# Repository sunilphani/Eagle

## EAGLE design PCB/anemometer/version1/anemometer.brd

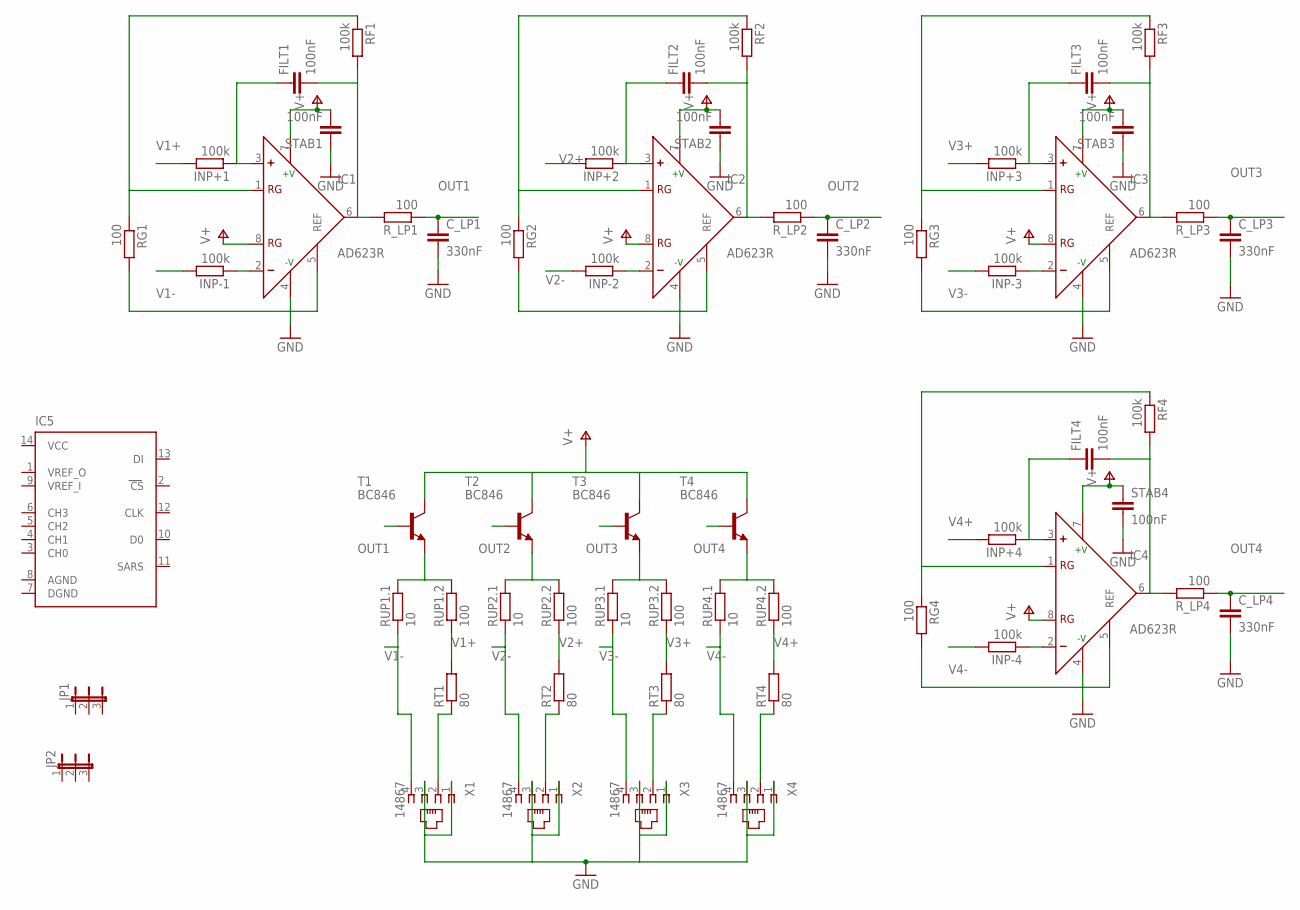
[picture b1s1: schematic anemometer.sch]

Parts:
C_LP1, C_LP2, C_LP3, C_LP4: 330nF; C1206
FILT1, FILT2, FILT3, FILT4: 100nF; C1206
IC1, IC2, IC3, IC4: AD623R; SO8
IC5: ADC08034D; SO14
INP+1, INP+2, INP+3, INP+4: 100k; M1206
INP-1, INP-2, INP-3, INP-4: 100k; M1206
JP1, JP2: JP2E; JP2
RF1, RF2, RF3, RF4: 100k; M1206
RG1, RG2, RG3, RG4: 100; M1206
RT1, RT2, RT3, RT4: 80; R1206
RUP1.1, RUP2.1, RUP3.1, RUP4.1: 10; R1206
RUP1.2, RUP2.2, RUP3.2, RUP4.2: 100; R1206
R_LP1, R_LP2, R_LP3, R_LP4: 100; M1206
STAB1, STAB2, STAB3, STAB4: 100nF; C1206
T1, T2, T3, T4: BC846; SOT23
X1, X2, X3, X4: 14867

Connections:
AGND: IC5.8 (AGND)
DGND: IC5.7 (DGND)
GND: C_LP1.2, C_LP2.2, C_LP3.2, C_LP4.2, IC1.4 (-V), IC1.5 (REF), IC2.4 (-V), IC2.5 (REF), IC3.4 (-V), IC3.5 (REF), IC4.4 (-V), IC4.5 (REF), RG1.2, RG2.2, RG3.2, RG4.2, STAB1.1, STAB2.1, STAB3.1, STAB4.2, X1.1, X1.3, X2.1, X2.3, X3.1, X3.3, X4.1, X4.3
unnamed: IC1.1 (RG), RF1.1, RG1.1
unnamed: IC4.1 (RG), RF4.1, RG4.1
unnamed: IC2.1 (RG), RF2.1, RG2.1
unnamed: IC3.1 (RG), RF3.1, RG3.1
unnamed: IC2.2 (-), INP-2.1
unnamed: IC1.2 (-), INP-1.1
unnamed: FILT2.1, IC2.3 (+), INP+2.1
unnamed: FILT3.1, IC3.3 (+), INP+3.1
unnamed: IC3.2 (-), INP-3.1
unnamed: FILT4.1, IC4.3 (+), INP+4.1
unnamed: IC4.2 (-), INP-4.1
unnamed: FILT1.1, IC1.3 (+), INP+1.1
OUT1: C_LP1.1, R_LP1.1, T1.1 (B)
OUT1.1: FILT1.2, IC1.6 (OUT), RF1.2, R_LP1.2
OUT2: C_LP2.1, R_LP2.1, T2.1 (B)
OUT2.1: FILT2.2, IC2.6 (OUT), RF2.2, R_LP2.2
OUT3: C_LP3.1, R_LP3.1, T3.1 (B)
OUT3.1: FILT3.2, IC3.6 (OUT), RF3.2, R_LP3.2
OUT4: C_LP4.1, R_LP4.1, T4.1 (B)
OUT4.1: FILT4.2, IC4.6 (OUT), RF4.2, R_LP4.2
REF1: RT1.1, X1.2
REF2: RT2.1, X2.2
REF3: RT3.1, X3.2
REF4: RT4.1, X4.2
SUPL1: RUP1.1.2, RUP1.2.2, T1.2 (E)
SUPL2: RUP2.1.2, RUP2.2.2, T2.2 (E)
SUPL3: RUP3.1.2, RUP3.2.2, T3.2 (E)
SUPL4: RUP4.1.2, RUP4.2.2, T4.2 (E)
V1+: INP+1.2, RT1.2, RUP1.2.1
V1-: INP-1.2, RUP1.1.1, X1.4
V2+: INP+2.2, RT2.2, RUP2.2.1
V2-: INP-2.2, RUP2.1.1, X2.4
V3+: INP+3.2, RT3.2, RUP3.2.1
V3-: INP-3.2, RUP3.1.1, X3.4
V4+: INP+4.2, RT4.2, RUP4.2.1
V4-: INP-4.2, RUP4.1.1, X4.4
V+: IC1.7 (+V), IC1.8 (RG), IC2.7 (+V), IC2.8 (RG), IC3.7 (+V), IC3.8 (RG), IC4.7 (+V), IC4.8 (RG), STAB1.2, STAB2.2, STAB3.2, STAB4.1, T1.3 (C), T2.3 (C), T3.3 (C), T4.3 (C)
VCC: IC5.14 (VCC)

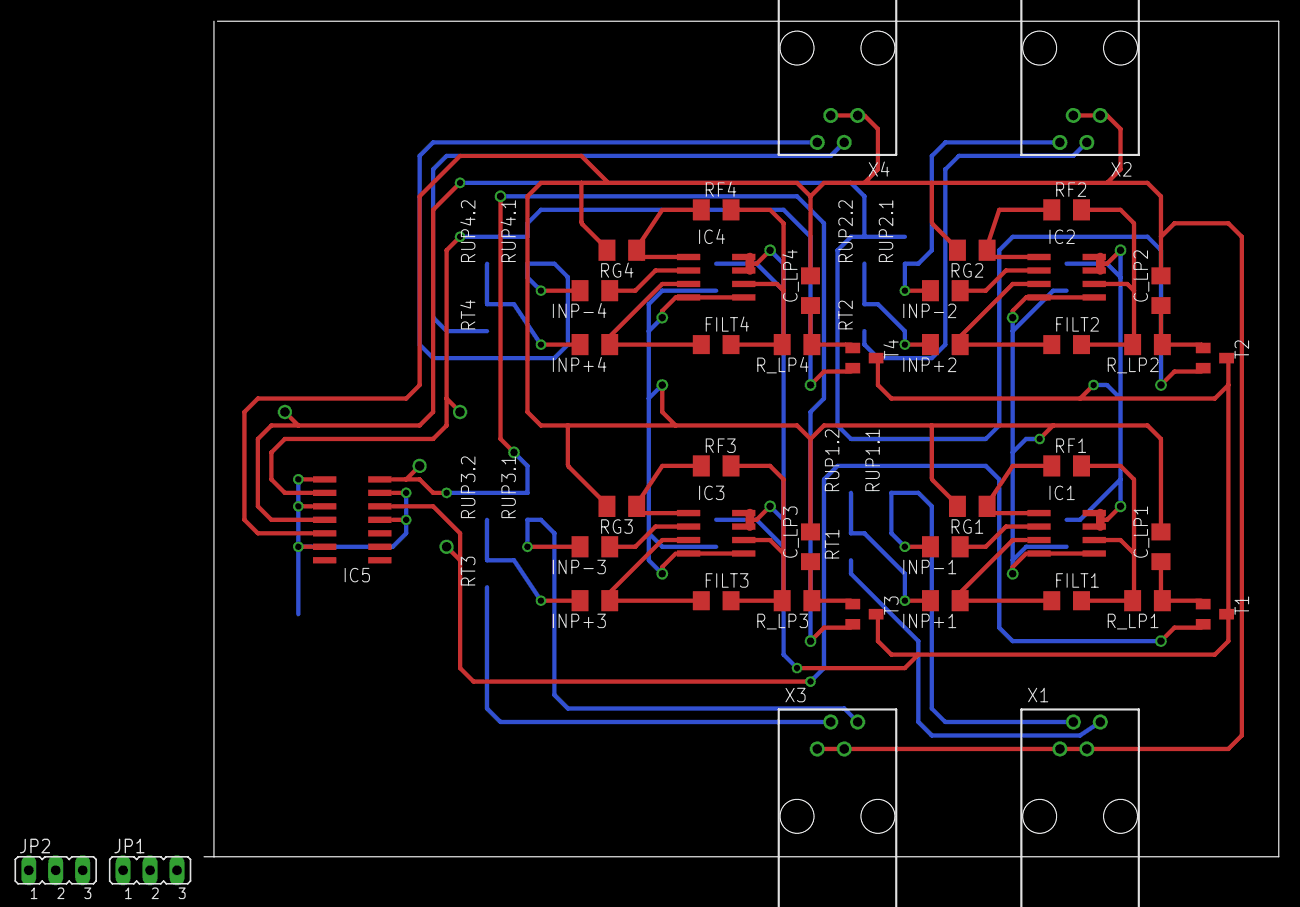
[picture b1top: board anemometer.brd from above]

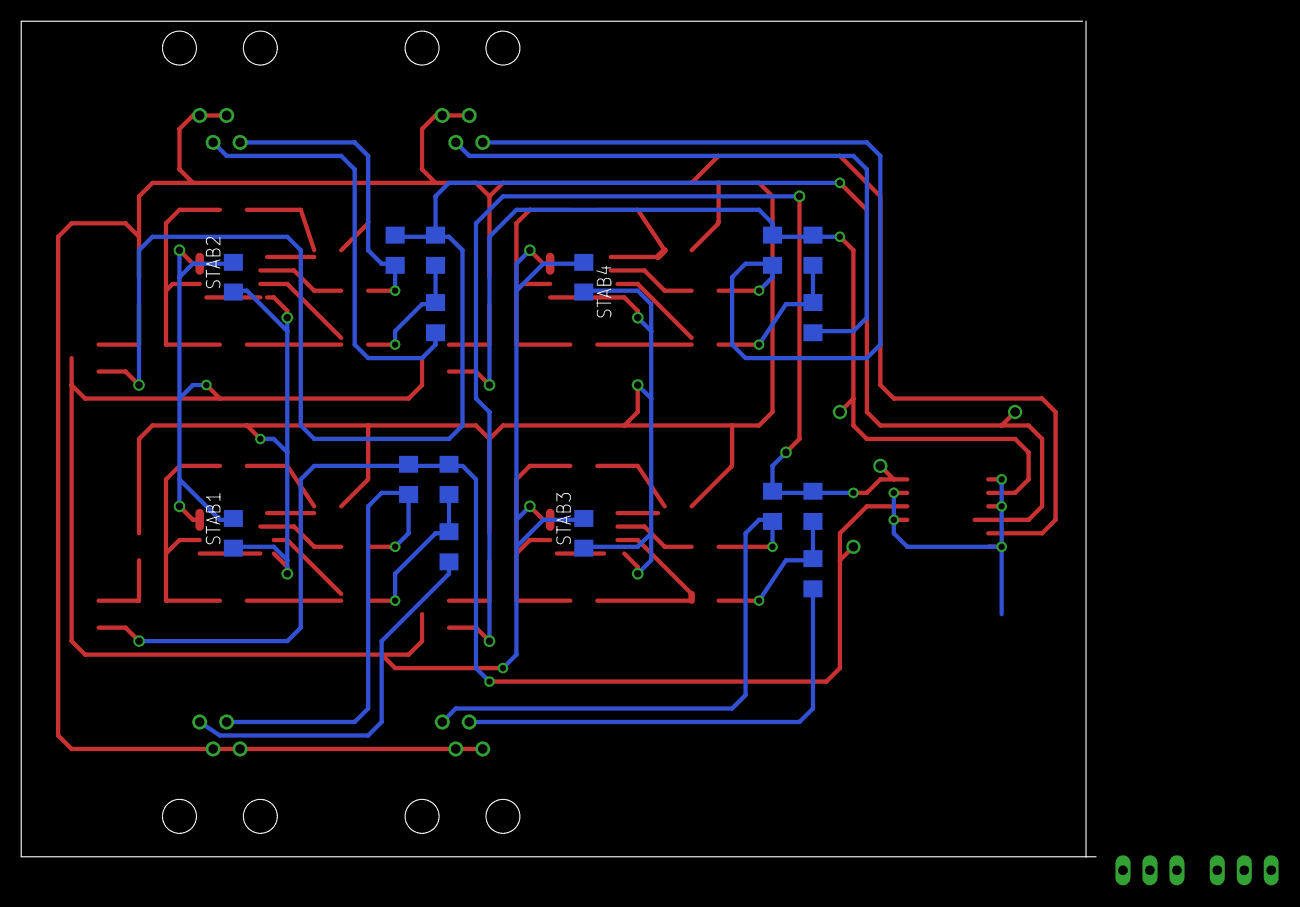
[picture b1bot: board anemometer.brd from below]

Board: 2 copper layers, 101.3 x 78.7 mm, 59 parts (4 on the bottom side), 38 nets.

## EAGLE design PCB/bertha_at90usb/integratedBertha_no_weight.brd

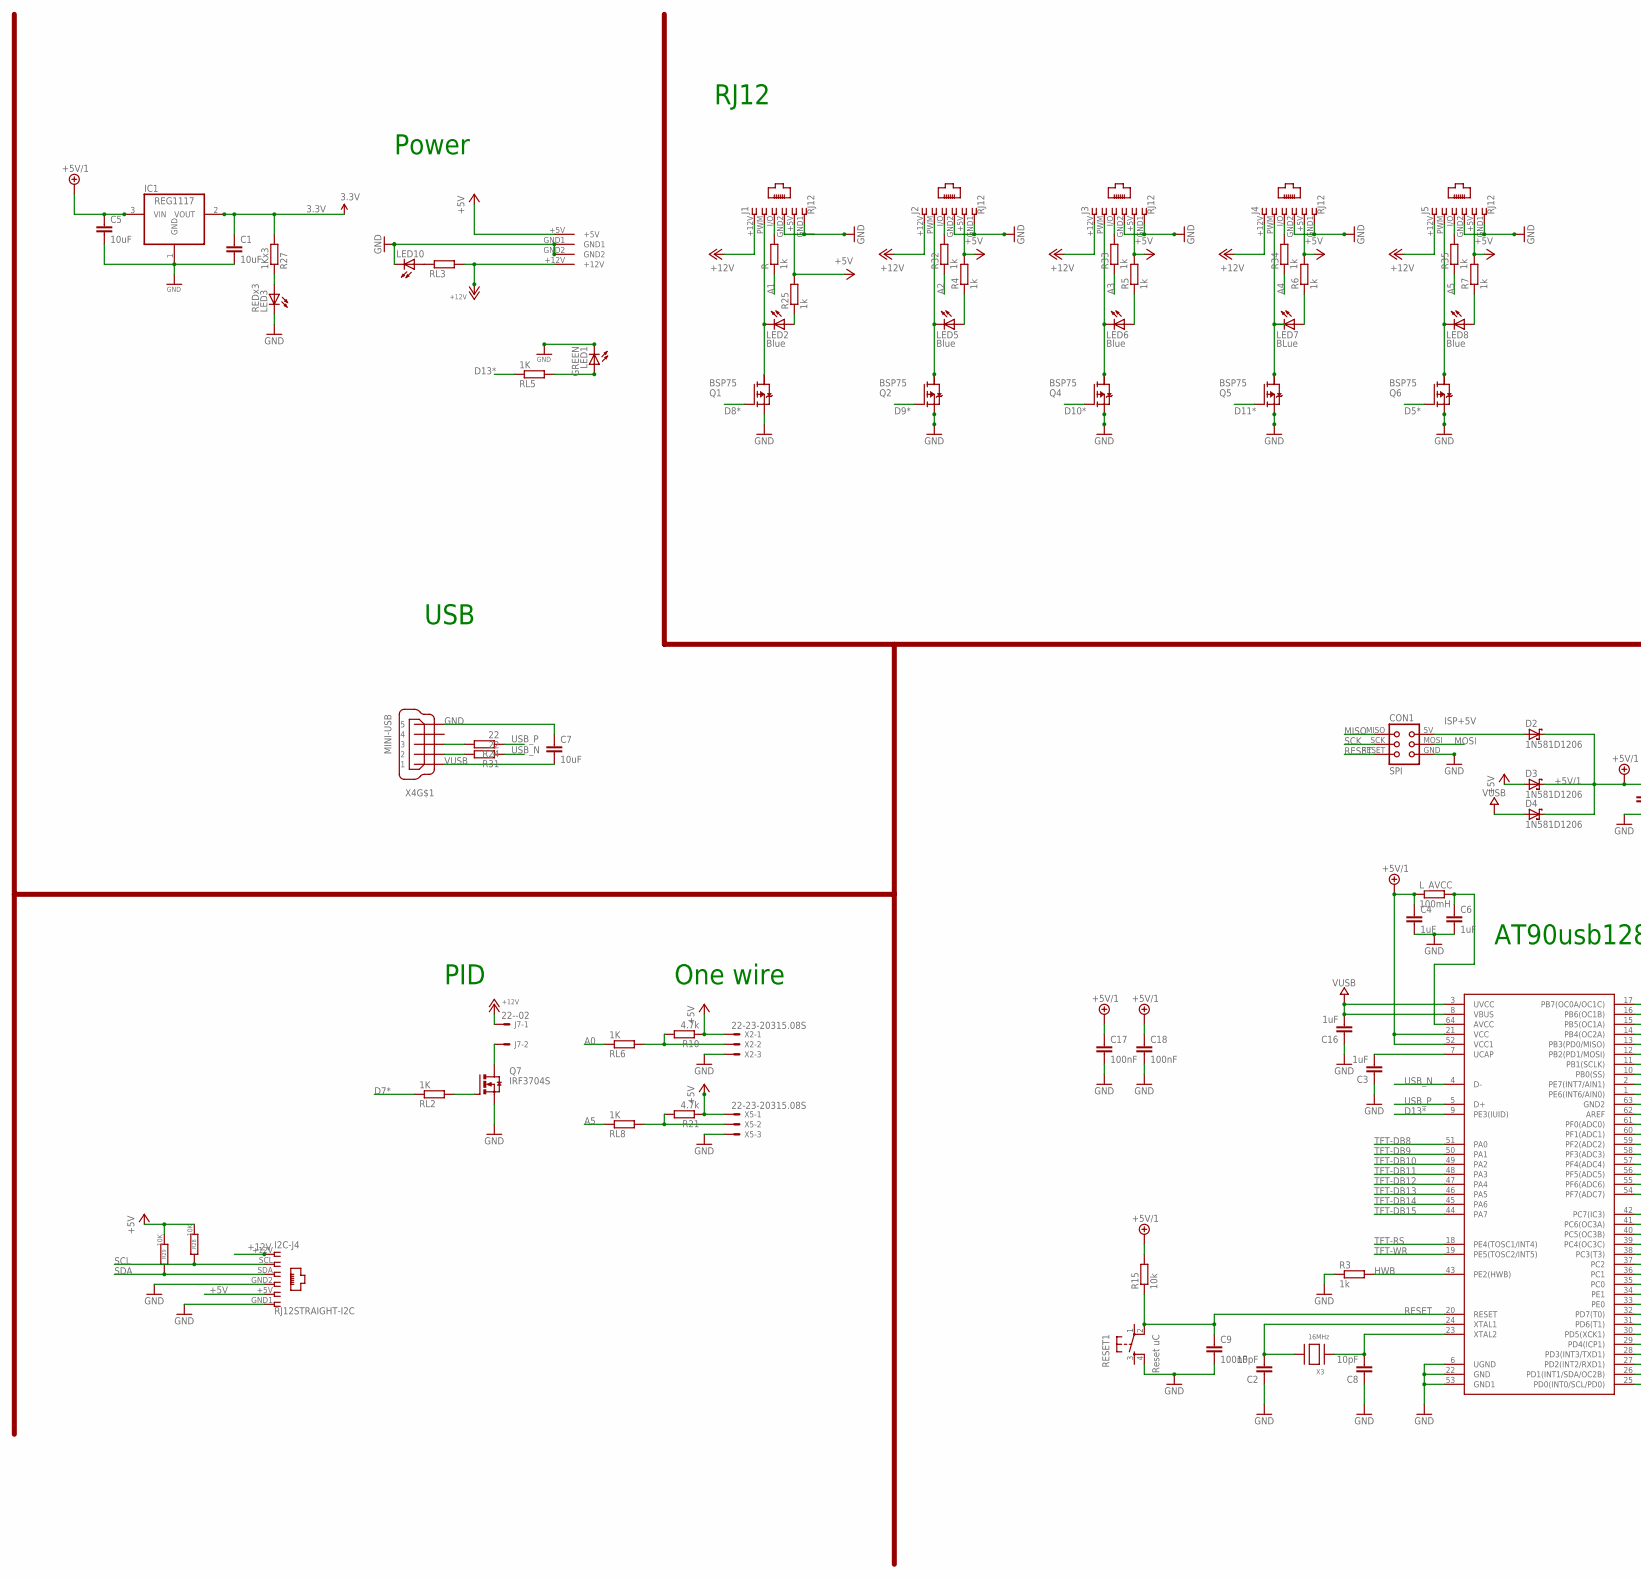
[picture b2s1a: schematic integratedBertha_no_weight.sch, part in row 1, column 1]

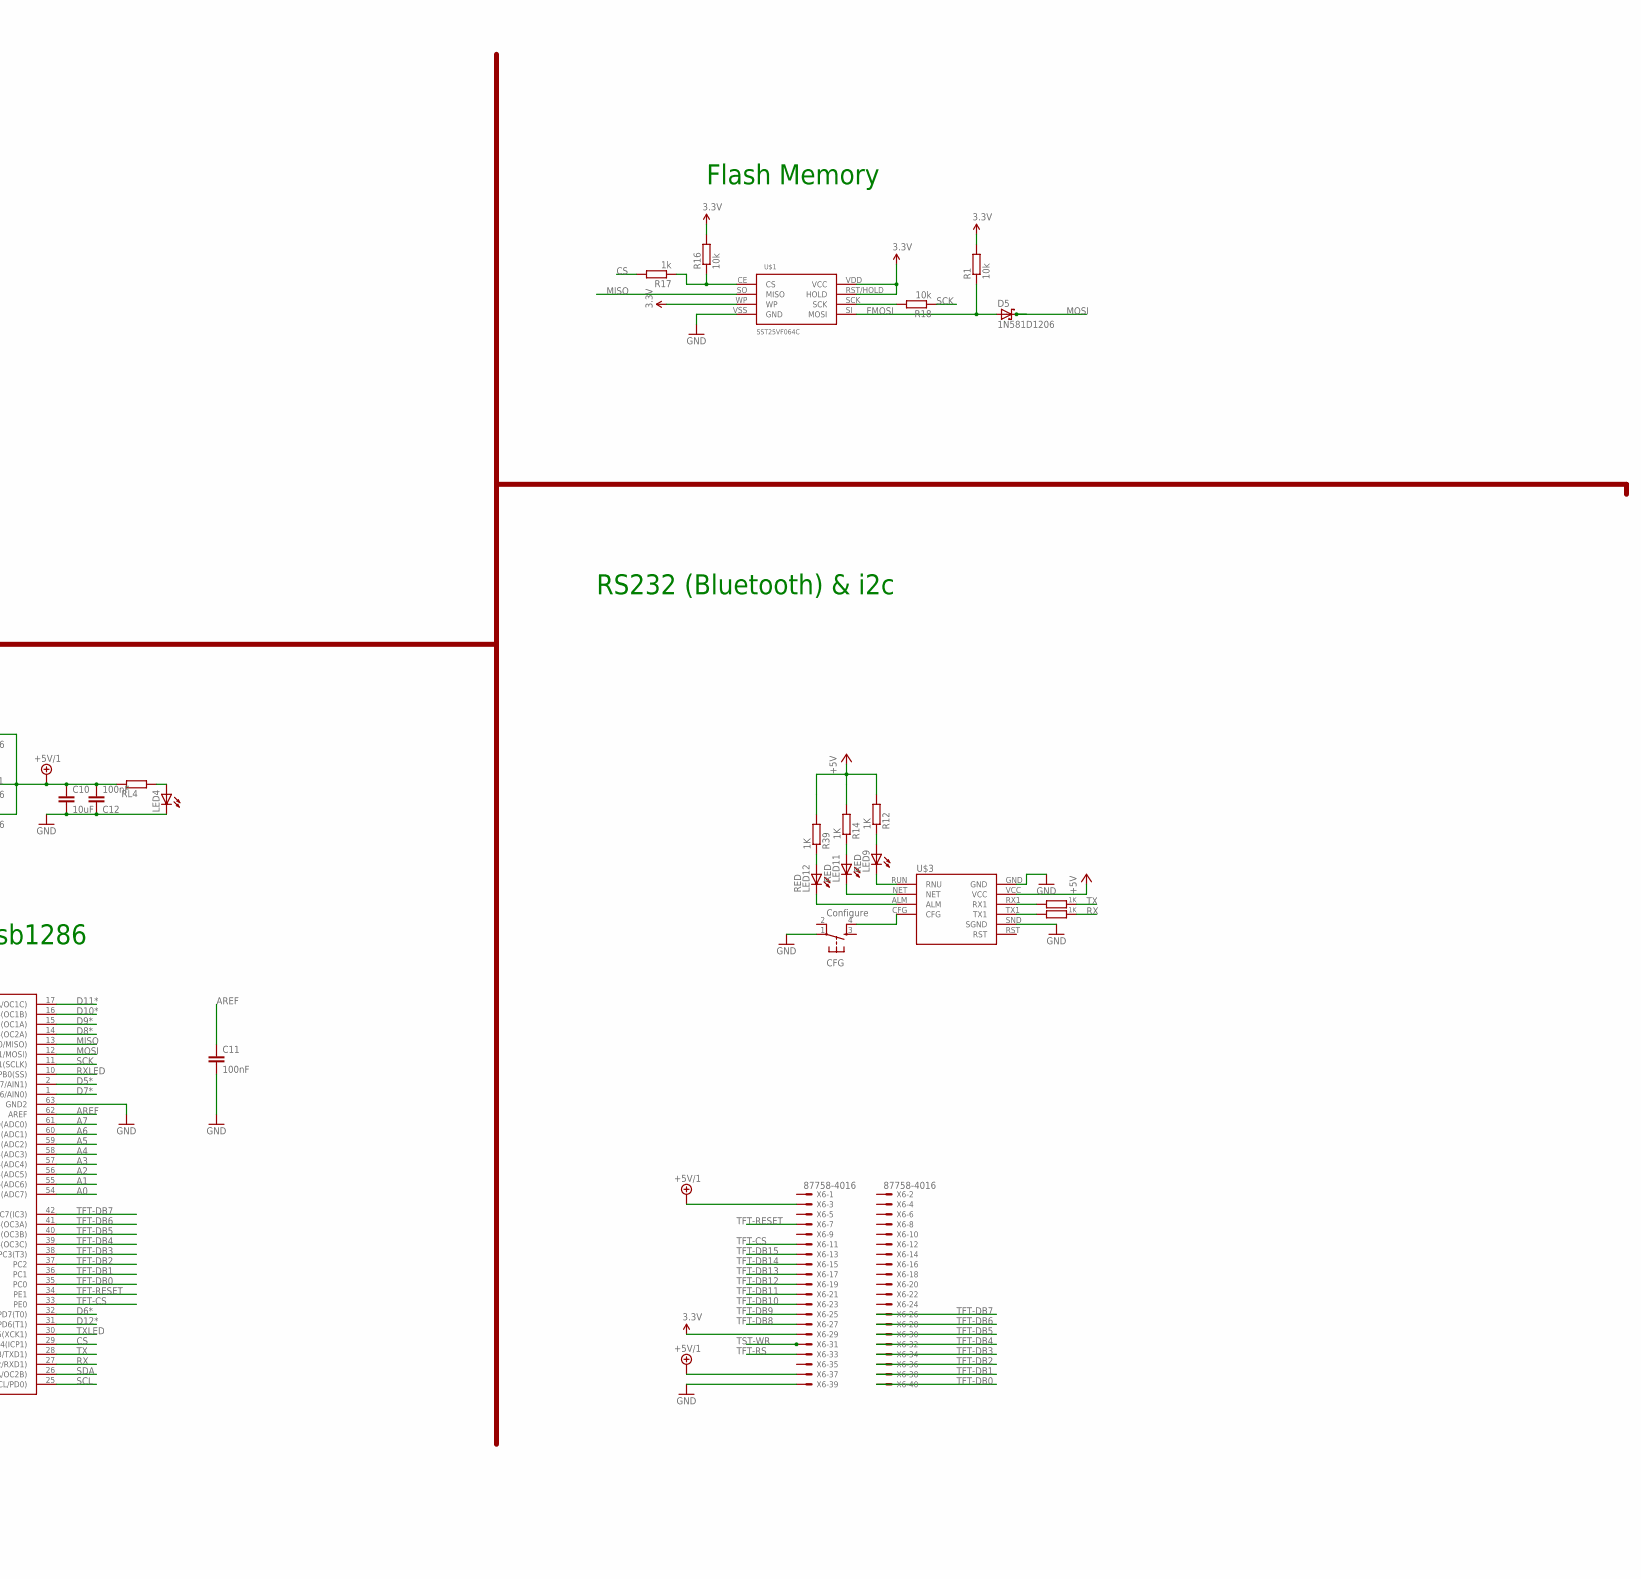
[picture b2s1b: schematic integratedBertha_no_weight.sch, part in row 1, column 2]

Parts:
C1, C5, C7, C10: 10uF; C1206
C2, C8: 10pF; C1206
C3, C4, C6, C16: 1uF; C1206
C9, C11, C12, C17, C18: 100nF; C1206
CFG: Configure; TACTILE_SWITCH_SMD
CON1: SPI; TC2030-MCP-NL
D2, D3, D4, D5: 1N581D1206; LED-1206
I2C-J4: RJ12STRAIGHT-I2C; RJ12-STRAIGHT-I2C
IC1: REG1117; SOT223
J1, J2, J3, J4, J5: RJ12; RJ12-STRAIGHT
J7: 22--02; 2-PIN-5.08S
LED1: GREEN; CHIPLED_1206
LED2, LED5, LED6, LED8: Blue; CHIPLED_1206
LED3: REDx3; CHIPLED_1206
LED4, LED10: LEDCHIPLED_1206; CHIPLED_1206
LED7: BLue; CHIPLED_1206
LED9, LED11, LED12: RED; CHIPLED_1206
L_AVCC: 100mH; R1206
Q1, Q2, Q4, Q5, Q6: BSP75; PG-SOT-223
Q7: IRF3704S; D2PACK
R, R4, R5, R6, R7, R17, R25, R32, R33, R34, R35: 1k; R0805
R1, R16, R18: 10k; R0805
R3: 1k; M0805
R8, R11, R12, R14, R39: 1K; R0805
R10, R21: 4.7k; R1206
R15: 10k; M0805
R24, R31: 22; M1206
R27: 1Kx3; R0805
R28, R29: 10K; M0805
RESET1: Reset uC; TACTILE_SWITCH_SMD
RL2, RL5, RL6, RL8: 1K; R0805
RL3, RL4: R-EU_R0805; R0805
U$1: SST25VF064C; SOIC_8-LEAD
U$2: AT90USB1286; TQFP64
U$3: SZ05-ZIGBEETHROUGHHOLE; SZ05-ZIGBEE4
U$6: KPJX-4S-S
X2, X5: 22-23-20315.08S; 3-PIN-5.08S
X3: 16MHz; NX6035
X4: MINI-USB; 32005-201
X6: 87758-4016

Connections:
3.3V: C1.1, IC1.2 (VOUT), R1.2, R16.2, R27.2, U$1.RST/HOLD (HOLD), U$1.VDD (VCC), U$1.WP, X6.29
+5V: D3.A, I2C-J4.+5V (5), J1.+5V (5), J2.+5V (5), J3.+5V (5), J4.+5V (5), J5.+5V (5), R4.2, R5.2, R6.2, R7.2, R10.1, R12.2, R14.2, R21.1, R25.2, R28.1, R29.1, R39.2, U$3.VCC, U$6.+5V, X2.1, X5.1
+5V/1: C4.1, C5.1, C10.1, C12.2, C17.1, C18.1, D2.C, D3.C, D4.C, IC1.3 (VIN), L_AVCC.1, R15.2, RL4.1, U$2.21 (VCC), U$2.52 (VCC1), X6.3, X6.37
+12V: I2C-J4.+12V (1), J1.+12V (1), J2.+12V (1), J3.+12V (1), J4.+12V (1), J5.+12V (1), J7.1, RL3.2, U$6.+12V
A0: RL6.1, U$2.54 (PF7(ADC7))
A1: R.1, U$2.55 (PF6(ADC6))
A2: R32.1, U$2.56 (PF5(ADC5))
A3: R33.1, U$2.57 (PF4(ADC4))
A4: R34.1, U$2.58 (PF3(ADC3))
A5: R35.1, RL8.1, U$2.59 (PF2(ADC2))
A6: U$2.60 (PF1(ADC1))
A7: U$2.61 (PF0(ADC0))
AREF: C11.1, U$2.62 (AREF)
CS: R17.2, U$2.29 (PD4(ICP1))
D5*: Q6.1 (G), U$2.2 (PE7(INT7/AIN1))
D6*: U$2.32 (PD7(T0))
D7*: RL2.1, U$2.1 (PE6(INT6/AIN0))
D8*: Q1.1 (G), U$2.14 (PB4(OC2A))
D9*: Q2.1 (G), U$2.15 (PB5(OC1A))
D10*: Q4.1 (G), U$2.16 (PB6(OC1B))
D11*: Q5.1 (G), U$2.17 (PB7(OC0A/OC1C))
D12*: U$2.31 (PD6(T1))
D13*: RL5.1, U$2.9 (PE3(IUID))
FMOSI: D5.A, R1.1, U$1.SI (MOSI)
GND: C1.2, C2.1, C3.1, C4.2, C5.2, C6.2, C7.1, C8.1, C9.2, C10.2, C11.2, C12.1, C16.1, C17.2, C18.2, CFG.1, CON1.GND, I2C-J4.GND1 (6), I2C-J4.GND2 (4), IC1.1 (GND), J1.GND1 (6), J1.GND2 (4), J2.GND1 (6), J2.GND2 (4), J3.GND1 (6), J3.GND2 (4), J4.GND1 (6), J4.GND2 (4), J5.GND1 (6), J5.GND2 (4), LED1.C, LED3.C, LED4.C, LED10.C, Q1.3 (S), Q2.3 (S), Q4.3 (S), Q5.3 (S), Q6.3 (S), Q7.3 (S), R3.1, RESET1.4, U$1.VSS (GND), U$2.6 (UGND), U$2.22 (GND), U$2.53 (GND1), U$2.63 (GND2), U$3.GND, U$3.SND (SGND), U$6.GND1, U$6.GND2, X2.3, X4.5, X5.3, X6.39
GND1: LED9.C, U$3.RUN (RNU)
GND2: LED11.C, U$3.NET
GND3: LED12.C, U$3.ALM
HWB: R3.2, U$2.43 (PE2(HWB))
ISP+5V: CON1.5V (VCC), D2.A
MISO: CON1.MISO, U$1.SO (MISO), U$2.13 (PB3(PD0/MISO))
MOSI: CON1.MOSI, D5.C, U$2.12 (PB2(PD1/MOSI))
unnamed: J3.PWM (2), LED6.C, Q4.2 (D)
unnamed: J2.I/O (3), R32.2
unnamed: LED1.A, RL5.2
unnamed: LED5.A, R4.1
unnamed: J4.PWM (2), LED7.C, Q5.2 (D)
unnamed: Q7.1 (G), RL2.2
unnamed: J3.I/O (3), R33.2
unnamed: C3.2, U$2.7 (UCAP)
unnamed: R21.2, RL8.2, X5.2
unnamed: R16.1, R17.1, U$1.CE (CS)
unnamed: R11.2, U$3.RX1
unnamed: LED4.A, RL4.2
unnamed: C6.1, L_AVCC.2, U$2.64 (AVCC)
unnamed: C2.2, U$2.24 (XTAL1), X3.P$2
unnamed: LED2.A, R25.1
unnamed: J1.I/O (3), R.2
unnamed: J5.PWM (2), LED8.C, Q6.2 (D)
unnamed: LED3.A, R27.1
unnamed: R10.2, RL6.2, X2.2
unnamed: LED6.A, R5.1
unnamed: R18.2, U$1.SCK
unnamed: R8.2, U$3.TX1
unnamed: LED9.A, R12.1
unnamed: LED11.A, R14.1
unnamed: LED12.A, R39.1
unnamed: J2.PWM (2), LED5.C, Q2.2 (D)
unnamed: J4.I/O (3), R34.2
unnamed: LED7.A, R6.1
unnamed: J5.I/O (3), R35.2
unnamed: LED8.A, R7.1
unnamed: J1.PWM (2), LED2.C, Q1.2 (D)
unnamed: CFG.4, U$3.CFG
unnamed: J7.2, Q7.2 (D)
unnamed: C8.2, U$2.23 (XTAL2), X3.P$1
unnamed: LED10.A, RL3.1
RESET: C9.1, CON1.RESET, R15.1, RESET1.2, U$2.20 (RESET)
RX: R8.1, U$2.27 (PD2(INT2/RXD1))
RXLED: U$2.10 (PB0(SS))
SCK: CON1.SCK, R18.1, U$2.11 (PB1(SCLK))
SCL: I2C-J4.SCL (2), R28.2, U$2.25 (PD0(INT0/SCL/PD0))
SDA: I2C-J4.SDA (3), R29.2, U$2.26 (PD1(INT1/SDA/OC2B))
TFT-CS: U$2.33 (PE0), X6.11
TFT-DB0: U$2.35 (PC0), X6.40
TFT-DB1: U$2.36 (PC1), X6.38
TFT-DB2: U$2.37 (PC2), X6.36
TFT-DB3: U$2.38 (PC3(T3)), X6.34
TFT-DB4: U$2.39 (PC4(OC3C)), X6.32
TFT-DB5: U$2.40 (PC5(OC3B)), X6.30
TFT-DB6: U$2.41 (PC6(OC3A)), X6.28
TFT-DB7: U$2.42 (PC7(IC3)), X6.26
TFT-DB8: U$2.51 (PA0), X6.27
TFT-DB9: U$2.50 (PA1), X6.25
TFT-DB10: U$2.49 (PA2), X6.23
TFT-DB11: U$2.48 (PA3), X6.21
TFT-DB12: U$2.47 (PA4), X6.19
TFT-DB13: U$2.46 (PA5), X6.17
TFT-DB14: U$2.45 (PA6), X6.15
TFT-DB15: U$2.44 (PA7), X6.13
TFT-RESET: U$2.34 (PE1), X6.7
TFT-RS: U$2.18 (PE4(TOSC1/INT4)), X6.33
TFT-WR: U$2.19 (PE5(TOSC2/INT5))
TST-WR: X6.31
TX: R11.1, U$2.28 (PD3(INT3/TXD1))
TXLED: U$2.30 (PD5(XCK1))
USBC_N: R31.2, X4.2
USBC_P: R24.2, X4.3
USB_N: R31.1, U$2.4 (D-)
USB_P: R24.1, U$2.5 (D+)
VUSB: C7.2, C16.2, D4.A, U$2.3 (UVCC), U$2.8 (VBUS), X4.1

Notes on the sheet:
Flash Memory
RJ12
AT90usb1286
USB
Power
RS232 (Bluetooth) & i2c
PID
One wire

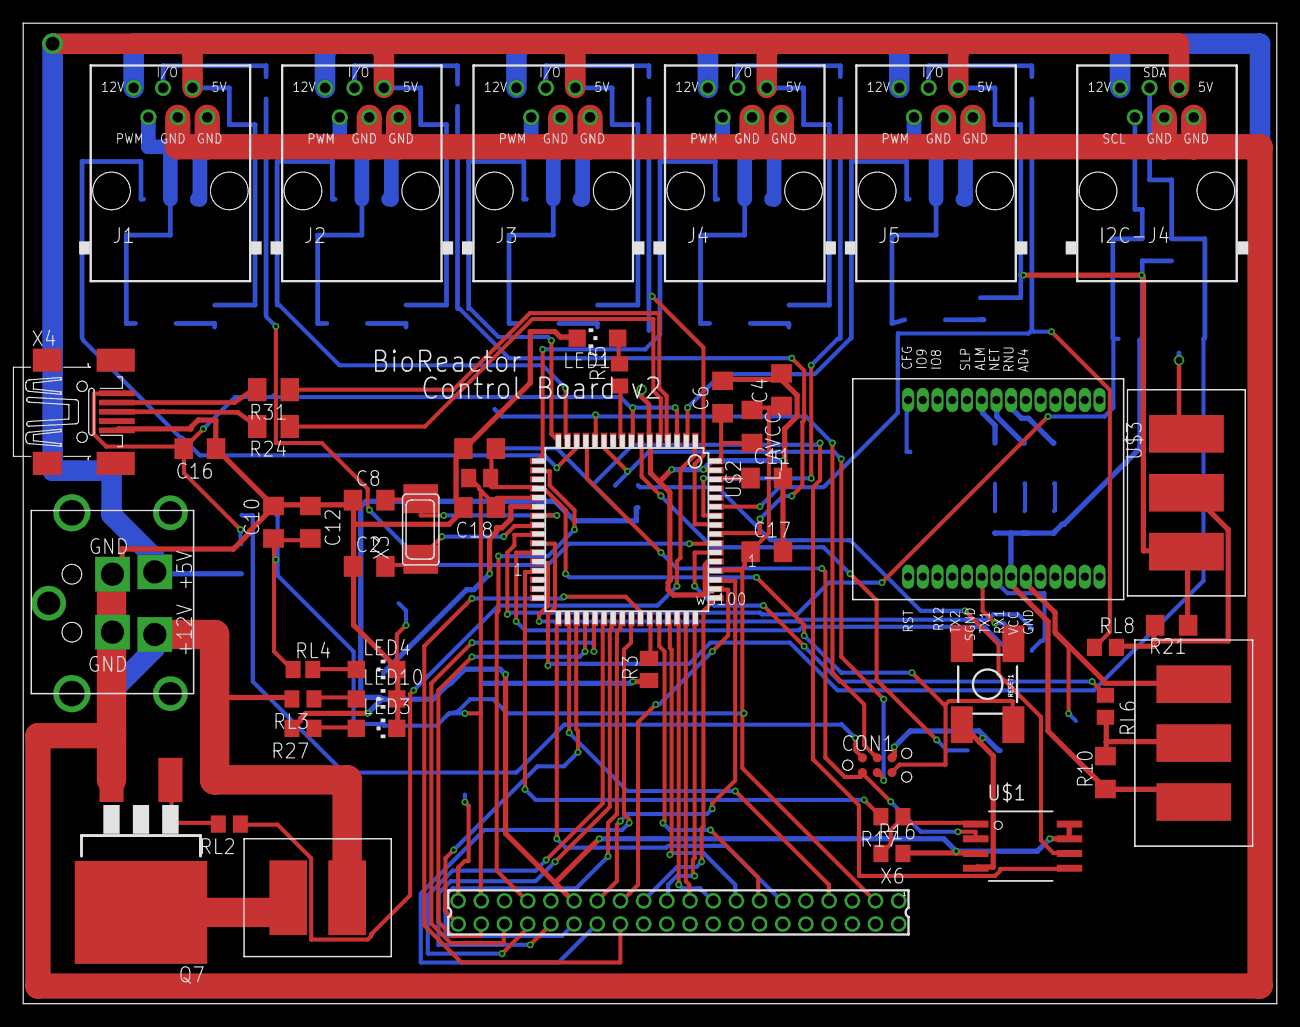
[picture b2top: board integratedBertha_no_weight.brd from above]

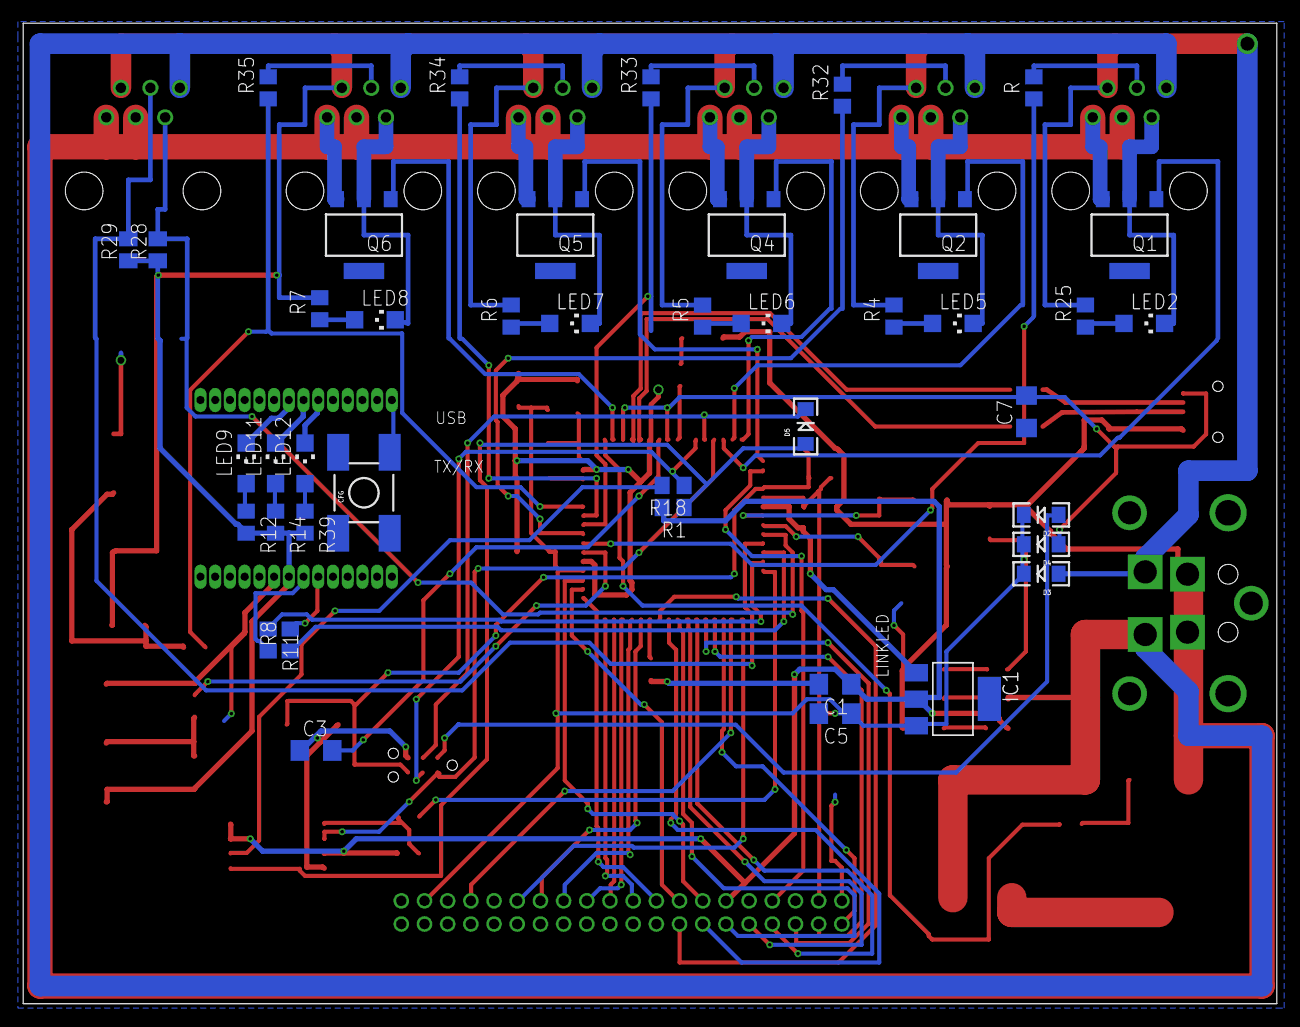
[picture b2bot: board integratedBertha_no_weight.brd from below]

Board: 4 copper layers, 108.1 x 84.6 mm, 92 parts (42 on the bottom side), 93 nets.

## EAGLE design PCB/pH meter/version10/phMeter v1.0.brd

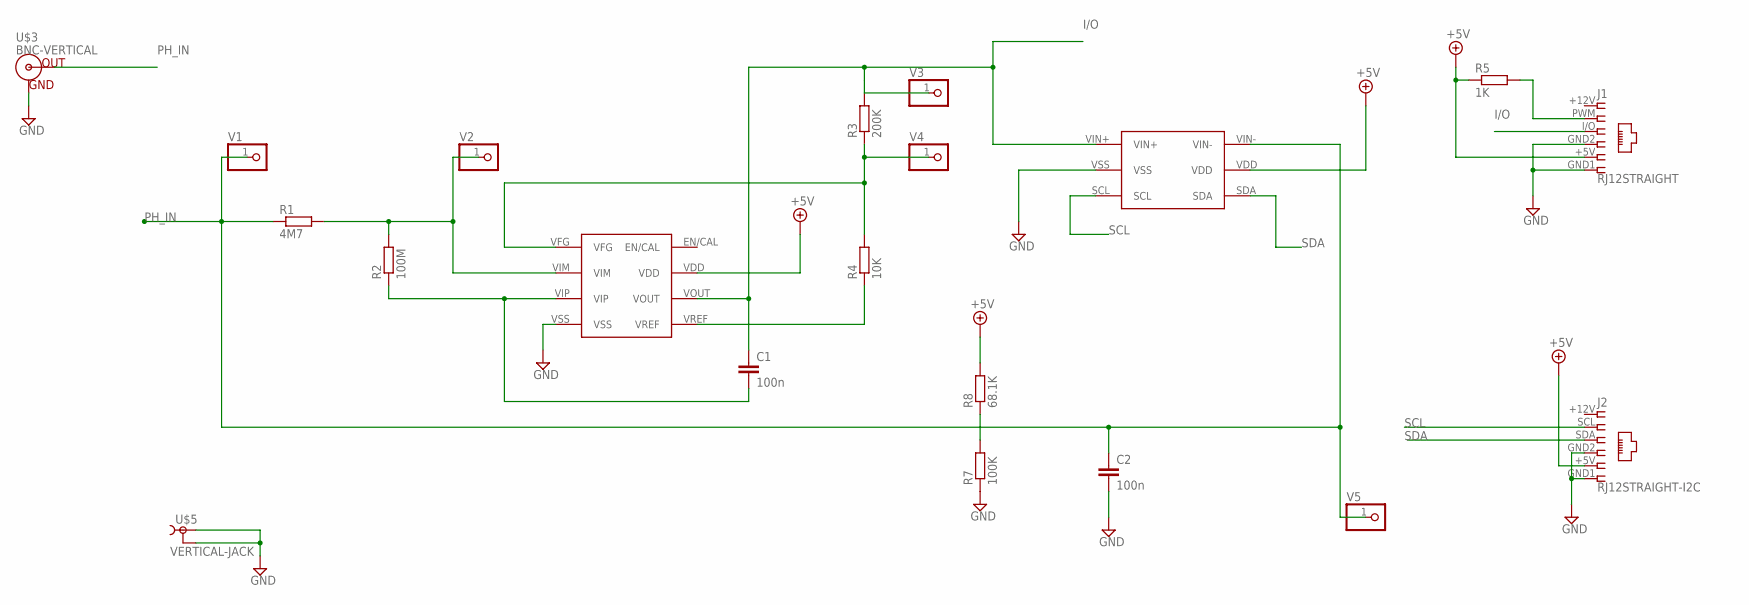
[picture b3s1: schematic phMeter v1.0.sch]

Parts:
C1, C2: 100n; C1206
J1: RJ12STRAIGHT; RJ12-STRAIGHT
J2: RJ12STRAIGHT-I2C; RJ12-STRAIGHT-I2C
R1: 4M7; R1206
R2: 100M; R1206
R3: 200K; R1206
R4: 10K; R1206
R5: 1K; R1206
R7: 100K; R1206
R8: 68.1K; R1206
U$1: MCP3425; SOT-23-6
U$2: MCP6N11010E; SOIC
U$3: BNC-VERTICAL
U$5: VERTICAL-JACK
V1, V2, V3, V4, V5: PINHD-1X1; 1X01

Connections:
+5V: J1.+5V (5), J2.+5V (5), R5.1, R8.2, U$1.VDD, U$2.VDD
GND: C2.2, J1.GND1 (6), J1.GND2 (4), J2.GND1 (6), J2.GND2 (4), R7.1, U$1.VSS, U$2.VSS, U$3.G (GND), U$5.P$1 (1), U$5.P$2 (2)
I/O: C1.1, J1.I/O (3), R3.2, U$1.VIN+, U$2.VOUT, V3.1
unnamed: R4.1, U$2.VREF
unnamed: J1.PWM (2), R5.2
unnamed: R3.1, R4.2, U$2.VFG, V4.1
unnamed: C1.2, R2.1, U$2.VIP
unnamed: R1.2, R2.2, U$2.VIM, V2.1
unnamed: R7.2, R8.1
PH_IN: C2.1, R1.1, U$1.VIN-, U$3.S (OUT), V1.1, V5.1
SCL: J2.SCL (2), U$1.SCL
SDA: J2.SDA (3), U$1.SDA

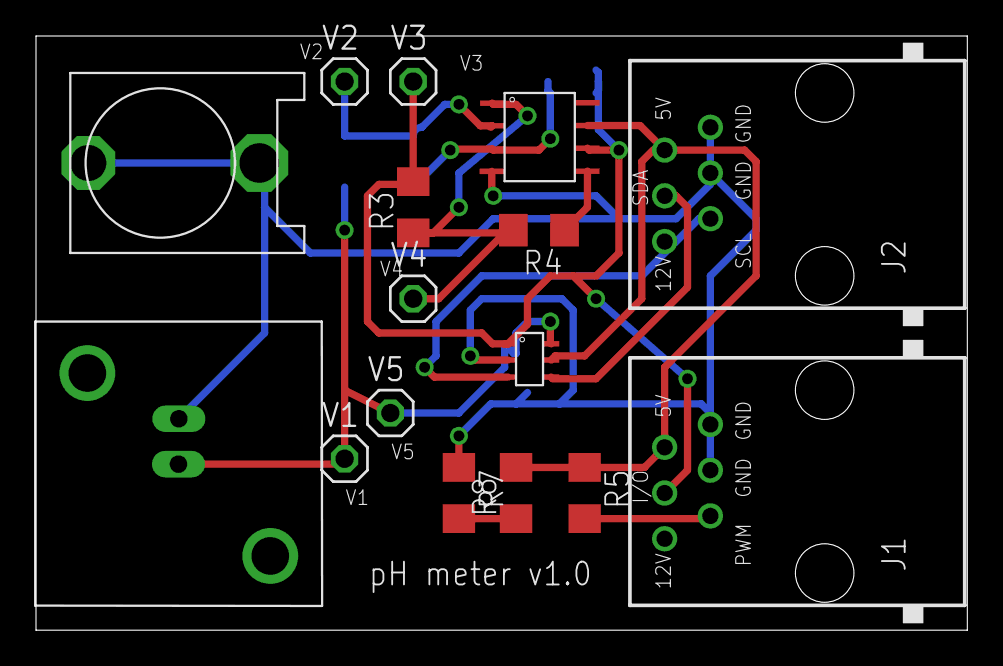
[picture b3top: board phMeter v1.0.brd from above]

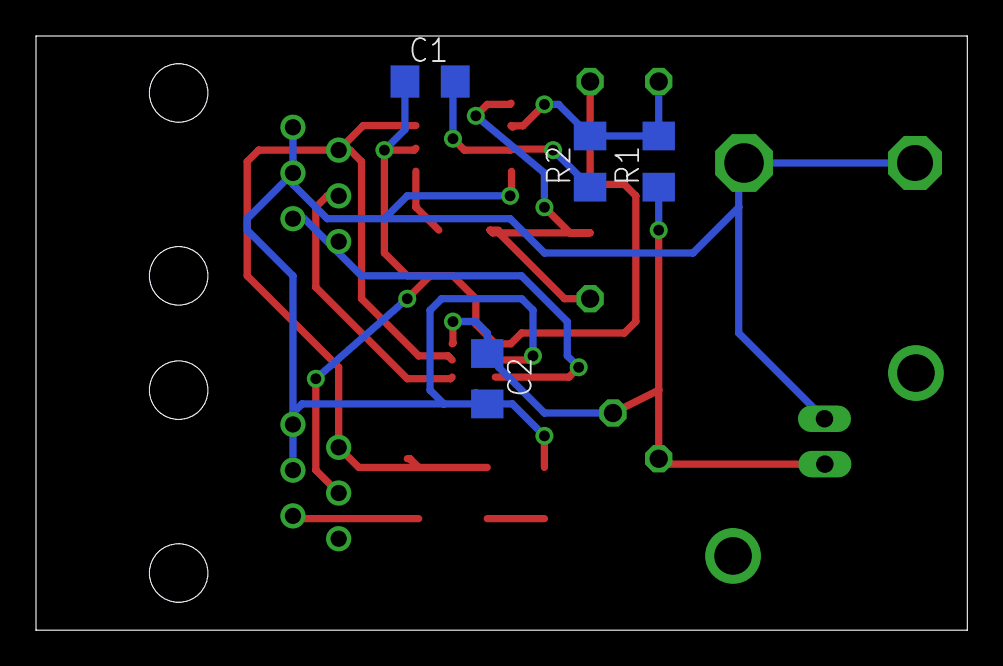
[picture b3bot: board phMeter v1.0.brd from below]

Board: 2 copper layers, 51.7 x 33.0 mm, 20 parts (4 on the bottom side), 12 nets.

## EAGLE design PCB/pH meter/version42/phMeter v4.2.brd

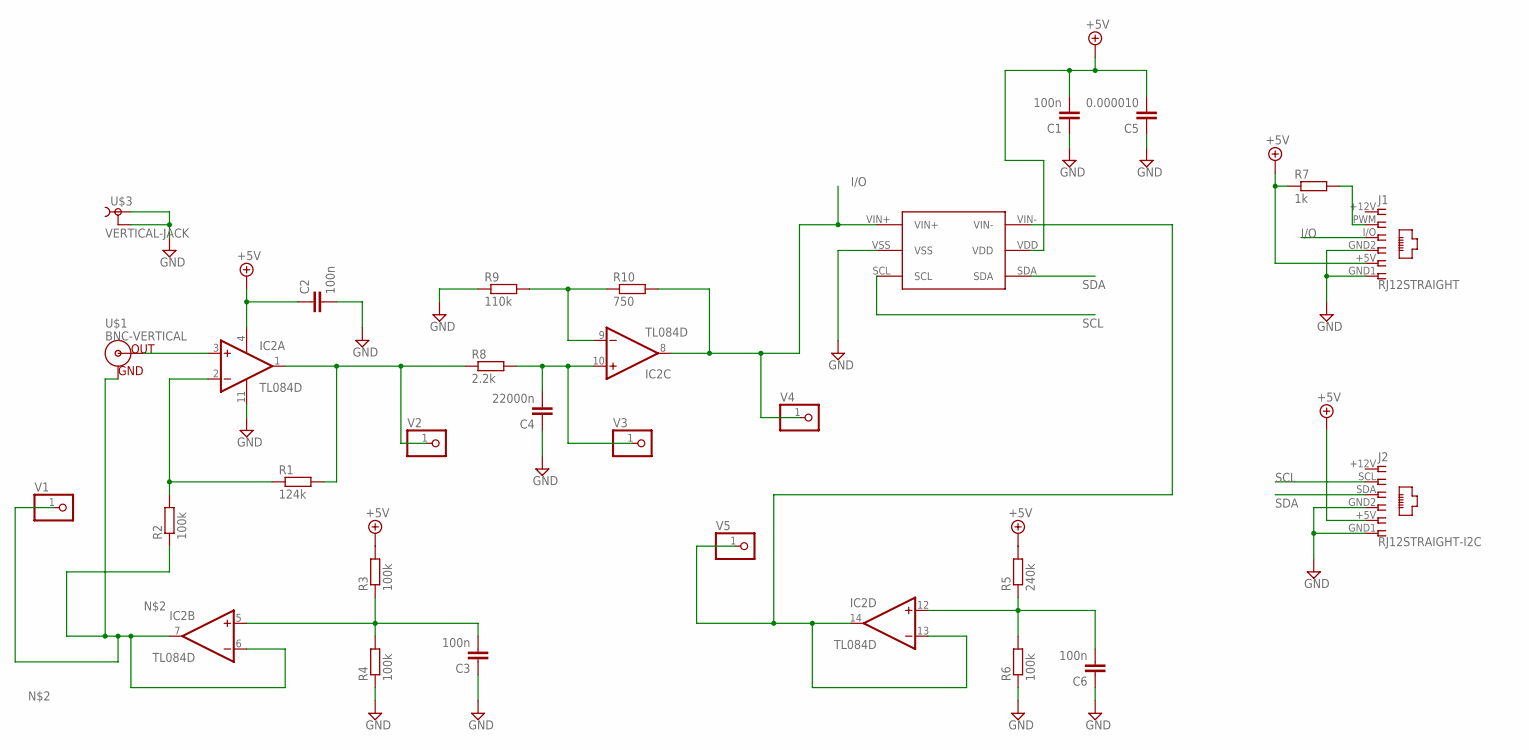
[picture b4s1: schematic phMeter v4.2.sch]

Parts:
C1, C2, C3, C6: 100n; C1206
C4: 22000n; C1206
C5: 0.000010; C1206
IC2: TL084D; SO14
J1: RJ12STRAIGHT; RJ12-STRAIGHT
J2: RJ12STRAIGHT-I2C; RJ12-STRAIGHT-I2C
R1: 124k; R1206
R2, R3, R4, R6: 100k; R1206
R5: 240k; R1206
R7: 1k; R1206
R8: 2.2k; R1206
R9: 110k; R1206
R10: 750; R1206
U$1: BNC-VERTICAL
U$3: VERTICAL-JACK
U$5: MCP3425; SOT-23-6
V1, V2, V3, V4, V5: PINHD-1X1; 1X01

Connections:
+5V: C1.2, C2.1, C5.2, IC2.4 (V+), J1.+5V (5), J2.+5V (5), R3.2, R5.2, R7.1, U$5.VDD
GND: C1.1, C2.2, C3.1, C4.1, C5.1, C6.1, IC2.11 (V-), J1.GND1 (6), J1.GND2 (4), J2.GND1 (6), J2.GND2 (4), R4.1, R6.1, R9.1, U$3.P$1 (1), U$3.P$2 (2), U$5.VSS
I/O: IC2.8 (OUT), J1.I/O (3), R10.2, U$5.VIN+, V4.1
unnamed: IC2.2 (-IN), R1.1, R2.2
unnamed: IC2.6 (-IN), IC2.7 (OUT), R2.1, U$1.G (GND), V1.1
unnamed: J1.PWM (2), R7.2
unnamed: IC2.13 (-IN), IC2.14 (OUT), U$5.VIN-, V5.1
unnamed: IC2.3 (+IN), U$1.S (OUT)
unnamed: IC2.1 (OUT), R1.2, R8.1, V2.1
unnamed: C3.2, IC2.5 (+IN), R3.1, R4.2
unnamed: C4.2, IC2.10 (+IN), R8.2, V3.1
unnamed: IC2.9 (-IN), R9.2, R10.1
unnamed: C6.2, IC2.12 (+IN), R5.1, R6.2
SCL: J2.SCL (2), U$5.SCL
SDA: J2.SDA (3), U$5.SDA

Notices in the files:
parts and their libraries:
lpatiny: ©2009 ROFA.cz - modified and updated by Robert Darlington ‹rdarlington@gmail.com›
SparkFun: Licensing: CC v3.0 Share-Alike You are welcome to use this library for commercial purposes.
